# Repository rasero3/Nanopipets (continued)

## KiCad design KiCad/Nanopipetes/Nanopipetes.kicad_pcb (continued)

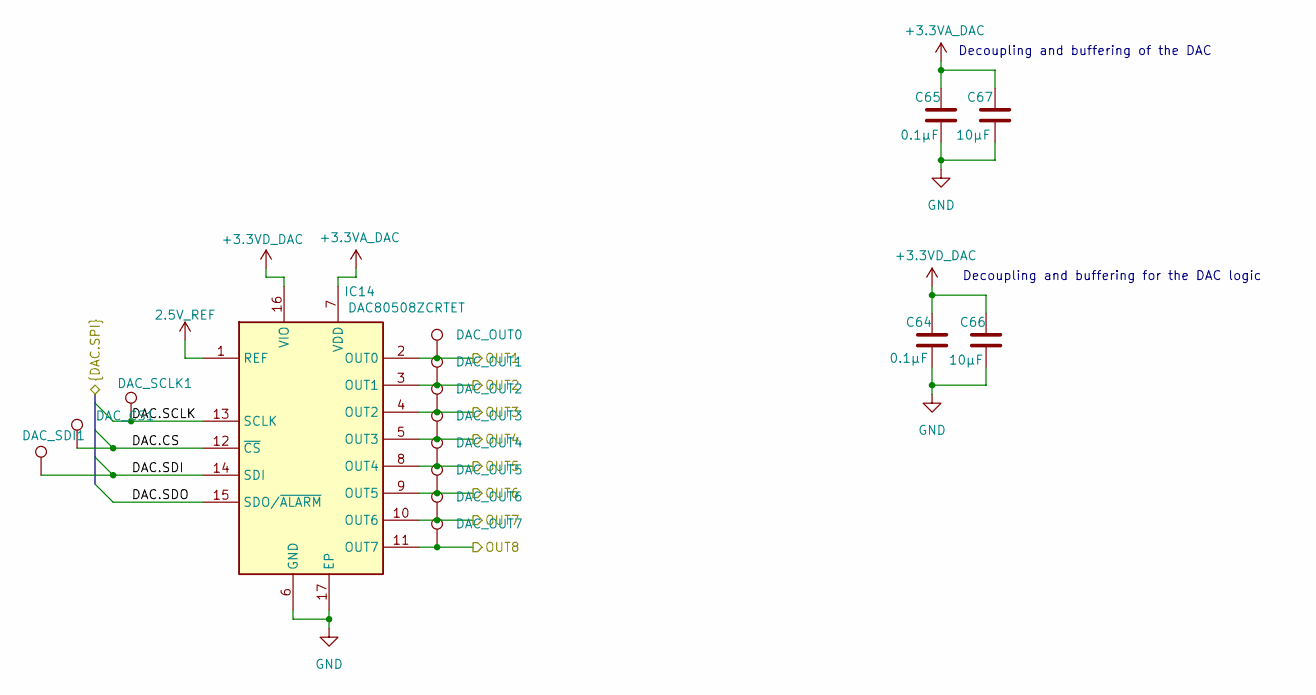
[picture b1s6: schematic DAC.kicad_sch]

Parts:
C64, C65: 0.1µF; C_0402_1005Metric; Mouser Part Number 581-0402YC104JAT4A
C66, C67: 10µF; C_0603_1608Metric; Mouser Part Number 80-C0603C106J3RACTU
DAC_CS1: TestPoint; TestPoint_Keystone_5000-5004_Miniature
DAC_OUT0, DAC_OUT1, DAC_OUT2, DAC_OUT3, DAC_OUT4, DAC_OUT5, DAC_OUT6, DAC_OUT7: TestPoint; TestPoint_Keystone_5000-5004_Miniature
DAC_SCLK1: TestPoint; TestPoint_Keystone_5000-5004_Miniature
DAC_SDI1: TestPoint; TestPoint_Keystone_5000-5004_Miniature
IC14: DAC80508ZCRTET; QFN50P300X300X80-17N; Manufacturer_Part_Number DAC80508ZCRTET; Mouser Part Number 595-DAC80508ZCRTET

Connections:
2.5V_REF: IC14.1 (REF); also elsewhere on the board
+3.3VA_ADC: C65.1, C67.1, IC14.7 (VDD); also elsewhere on the board
+3.3VD_ADC: C64.1, C66.1, IC14.16 (VIO); also elsewhere on the board
/DAC/DAC.CS: DAC_CS1.1, IC14.12 (~CS); also elsewhere on the board
/DAC/DAC.SCLK: DAC_SCLK1.1, IC14.13 (SCLK); also elsewhere on the board
/DAC/DAC.SDI: DAC_SDI1.1, IC14.14 (SDI); also elsewhere on the board
/DAC/DAC.SDO: IC14.15 (SDO/~ALARM); also elsewhere on the board
/DAC/OUT1: DAC_OUT0.1, IC14.2 (OUT0); also elsewhere on the board
/DAC/OUT2: DAC_OUT1.1, IC14.3 (OUT1); also elsewhere on the board
/DAC/OUT3: DAC_OUT2.1, IC14.4 (OUT2); also elsewhere on the board
/DAC/OUT4: DAC_OUT3.1, IC14.5 (OUT3); also elsewhere on the board
/DAC/OUT5: DAC_OUT4.1, IC14.8 (OUT4); also elsewhere on the board
/DAC/OUT6: DAC_OUT5.1, IC14.9 (OUT5); also elsewhere on the board
/DAC/OUT7: DAC_OUT6.1, IC14.10 (OUT6); also elsewhere on the board
/DAC/OUT8: DAC_OUT7.1, IC14.11 (OUT7); also elsewhere on the board
GND: C64.2, C65.2, C66.2, C67.2, IC14.6 (GND), IC14.17 (EP); also elsewhere on the board

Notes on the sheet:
Decoupling and buffering of the DAC
Decoupling and buffering for the DAC logic

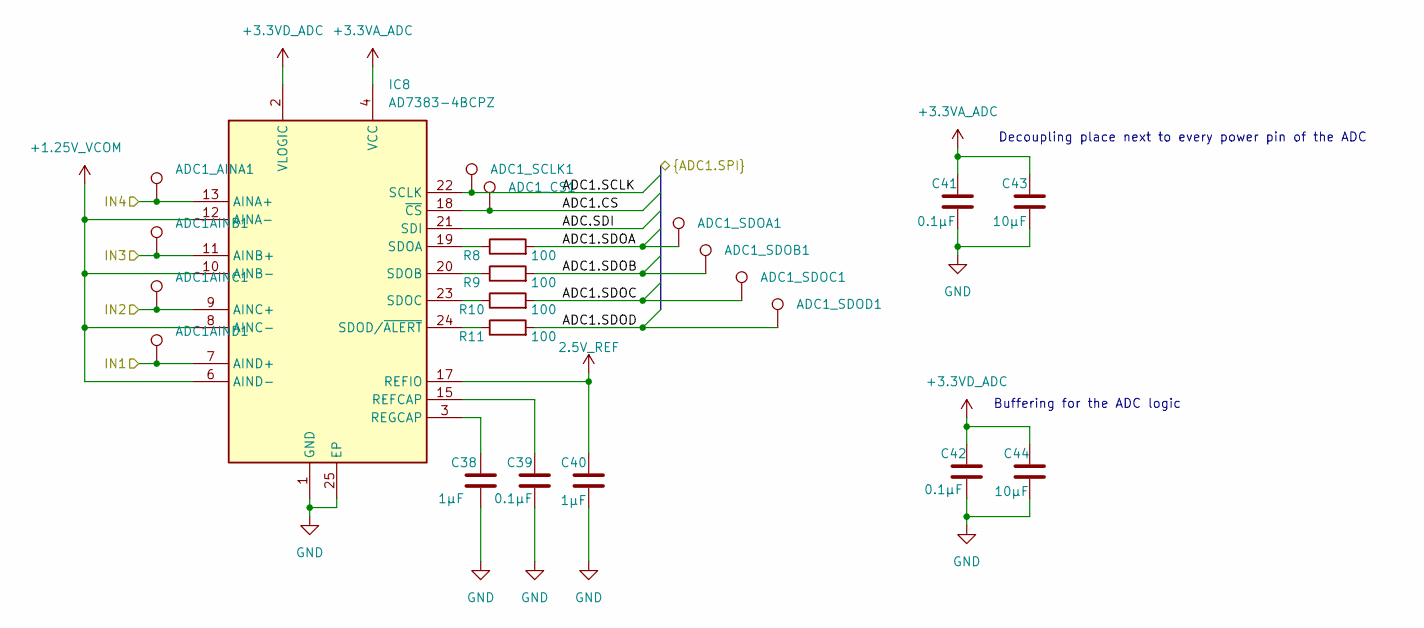
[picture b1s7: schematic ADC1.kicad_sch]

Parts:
ADC1AINB1, ADC1AINC1, ADC1AIND1, ADC1_AINA1, ADC1_CS1, ADC1_SCLK1, ADC1_SDOA1, ADC1_SDOB1, ADC1_SDOC1, ADC1_SDOD1: TestPoint; TestPoint_Keystone_5000-5004_Miniature
C38: 1µF; C_0402_1005Metric; Mouser Part Number 581-0402YC104JAT4A
C39, C41, C42: 0.1µF; C_0402_1005Metric; Mouser Part Number 581-0402YC104JAT4A
C40: 1µF; C_0603_1608Metric; Mouser Part Number 581-KGM15BR71A105JT
C43, C44: 10µF; C_0603_1608Metric; Mouser Part Number 80-C0603C106J3RACTU
IC8: AD7383-4BCPZ; QFN50P400X400X60-25N-D; Manufacturer_Part_Number AD7383-4BCPZ; Mouser Part Number 584-AD7383-4BCPZ
R8, R9, R10, R11: 100; R_0603_1608Metric; Mouser Part Number 71-RCG0603100RJNEA

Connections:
2.5V_REF: C40.1, IC8.17 (REFIO); also elsewhere on the board
+1.25V_VCOM: IC8.6 (AIND-), IC8.8 (AINC-), IC8.10 (AINB-), IC8.12 (AINA-); also elsewhere on the board
+3.3VA_ADC: C41.1, C43.1, IC8.4 (VCC); also elsewhere on the board
+3.3VD_ADC: C42.1, C44.1, IC8.2 (VLOGIC); also elsewhere on the board
/ADC1/ADC1.CS: ADC1_CS1.1, IC8.18 (~CS); also elsewhere on the board
/ADC1/ADC1.SCLK: ADC1_SCLK1.1, IC8.22 (SCLK); also elsewhere on the board
/ADC1/ADC1.SDOA: ADC1_SDOA1.1, R8.2; also elsewhere on the board
/ADC1/ADC1.SDOB: ADC1_SDOB1.1, R9.2; also elsewhere on the board
/ADC1/ADC1.SDOC: ADC1_SDOC1.1, R10.2; also elsewhere on the board
/ADC1/ADC1.SDOD: ADC1_SDOD1.1, R11.2; also elsewhere on the board
/ADC1/ADC.SDI: IC8.21 (SDI); also elsewhere on the board
/ADC1/IN1: ADC1AIND1.1, IC8.7 (AIND+); also elsewhere on the board
/ADC1/IN2: ADC1AINC1.1, IC8.9 (AINC+); also elsewhere on the board
/ADC1/IN3: ADC1AINB1.1, IC8.11 (AINB+); also elsewhere on the board
/ADC1/IN4: ADC1_AINA1.1, IC8.13 (AINA+); also elsewhere on the board
GND: C38.2, C39.2, C40.2, C41.2, C42.2, C43.2, C44.2, IC8.1 (GND), IC8.5 (GND_2), IC8.14 (GND_3), IC8.16 (GND_4), IC8.25 (EP); also elsewhere on the board
unnamed: C39.1, IC8.15 (REFCAP)
unnamed: C38.1, IC8.3 (REGCAP)
unnamed: IC8.19 (SDOA), R8.1
unnamed: IC8.20 (SDOB), R9.1
unnamed: IC8.23 (SDOC), R10.1
unnamed: IC8.24 (SDOD/~ALERT), R11.1

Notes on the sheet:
Buffering for the ADC logic
Decoupling place next to every power pin of the ADC

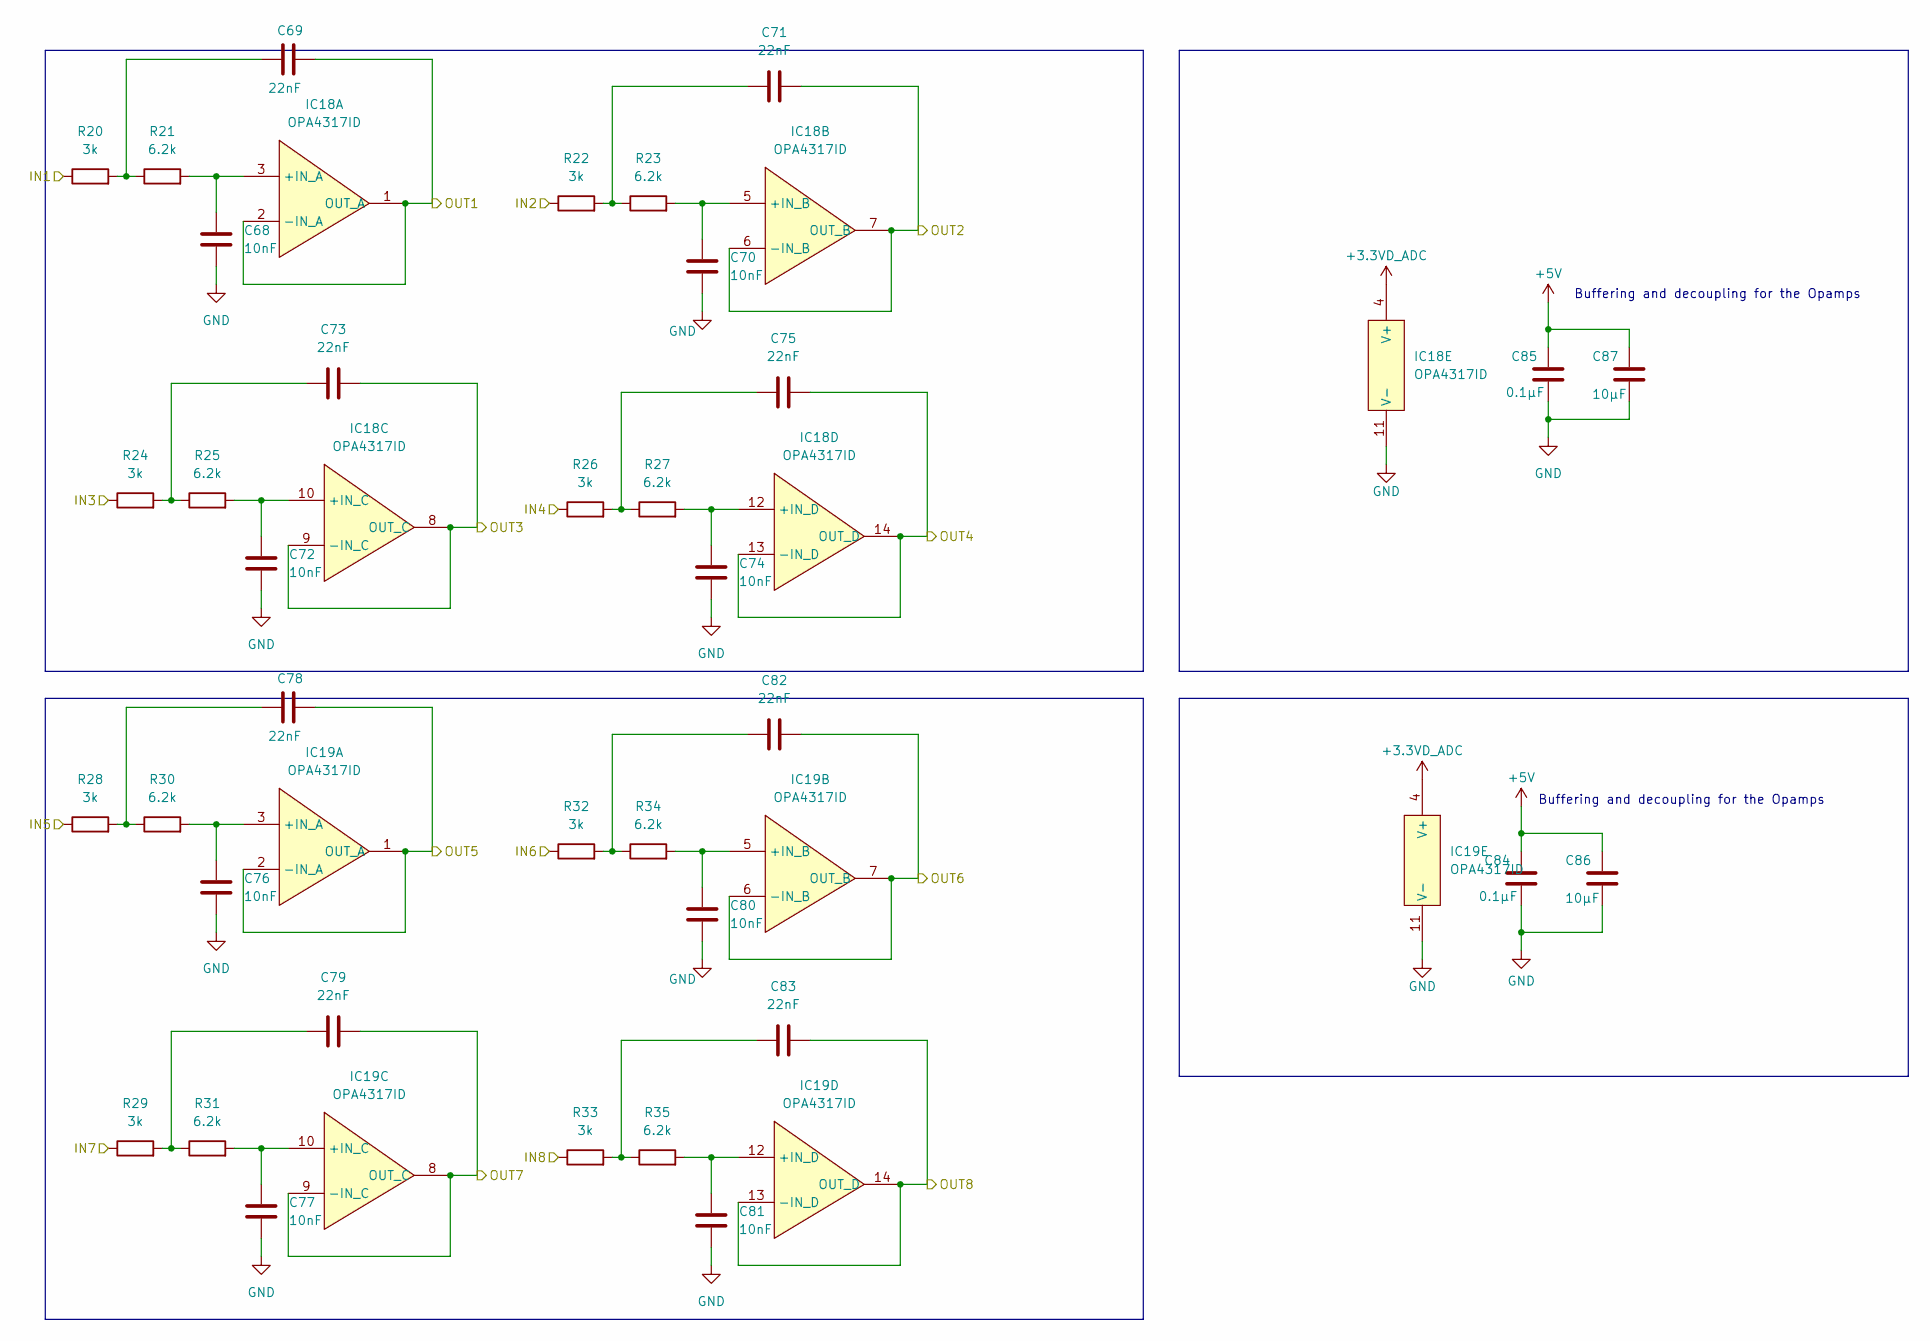
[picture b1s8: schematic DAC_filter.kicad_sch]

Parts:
C68, C70, C72, C74, C76, C77, C80, C81: 10nF; C_0402_1005Metric; Mouser Part Number 77-VJ0402Y103JXXAC
C69, C71, C73, C75, C78, C79, C82, C83: 22nF; C_0402_1005Metric; Mouser Part Number 581-04023C223JAT2A
C84, C85: 0.1µF; C_0402_1005Metric; Mouser Part Number 581-0402YC104JAT4A
C86, C87: 10µF; C_0603_1608Metric; Mouser Part Number 80-C0603C106J3RACTU
IC18, IC19: OPA4317ID; SOIC127P600X175-14N; Mouser Part Number 595-OPA4317ID
R20, R22, R24, R26, R28, R29, R32, R33: 3k; R_0603_1608Metric; Mouser Part Number 603-AR0603JR-073KL
R21, R23, R25, R27, R30, R31, R34, R35: 6.2k; R_0603_1608Metric; Mouser Part Number 603-AC0603JR-076K2L

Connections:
+3.3VD_ADC: IC18.4 (V+), IC19.4 (V+); also elsewhere on the board
+5V: C84.1, C85.1, C86.1, C87.1; also elsewhere on the board
/Connectors/OUT1: C69.2, IC18.1 (OUT_A), IC18.2 (-IN_A); also elsewhere on the board
/Connectors/OUT2: C71.2, IC18.6 (-IN_B), IC18.7 (OUT_B); also elsewhere on the board
/Connectors/OUT3: C73.2, IC18.8 (OUT_C), IC18.9 (-IN_C); also elsewhere on the board
/Connectors/OUT4: C75.2, IC18.13 (-IN_D), IC18.14 (OUT_D); also elsewhere on the board
/Connectors/OUT5: C78.2, IC19.1 (OUT_A), IC19.2 (-IN_A); also elsewhere on the board
/Connectors/OUT6: C82.2, IC19.6 (-IN_B), IC19.7 (OUT_B); also elsewhere on the board
/Connectors/OUT7: C79.2, IC19.8 (OUT_C), IC19.9 (-IN_C); also elsewhere on the board
/Connectors/OUT8: C83.2, IC19.13 (-IN_D), IC19.14 (OUT_D); also elsewhere on the board
/DAC/OUT1: R20.1; also elsewhere on the board
/DAC/OUT2: R22.1; also elsewhere on the board
/DAC/OUT3: R24.1; also elsewhere on the board
/DAC/OUT4: R26.1; also elsewhere on the board
/DAC/OUT5: R28.1; also elsewhere on the board
/DAC/OUT6: R32.1; also elsewhere on the board
/DAC/OUT7: R29.1; also elsewhere on the board
/DAC/OUT8: R33.1; also elsewhere on the board
GND: C68.2, C70.2, C72.2, C74.2, C76.2, C77.2, C80.2, C81.2, C84.2, C85.2, C86.2, C87.2, IC18.11 (V-), IC19.11 (V-); also elsewhere on the board
unnamed: C69.1, R20.2, R21.1
unnamed: C71.1, R22.2, R23.1
unnamed: C73.1, R24.2, R25.1
unnamed: C75.1, R26.2, R27.1
unnamed: C78.1, R28.2, R30.1
unnamed: C79.1, R29.2, R31.1
unnamed: C82.1, R32.2, R34.1
unnamed: C83.1, R33.2, R35.1
unnamed: C68.1, IC18.3 (+IN_A), R21.2
unnamed: C70.1, IC18.5 (+IN_B), R23.2
unnamed: C72.1, IC18.10 (+IN_C), R25.2
unnamed: C74.1, IC18.12 (+IN_D), R27.2
unnamed: C76.1, IC19.3 (+IN_A), R30.2
unnamed: C80.1, IC19.5 (+IN_B), R34.2
unnamed: C77.1, IC19.10 (+IN_C), R31.2
unnamed: C81.1, IC19.12 (+IN_D), R35.2

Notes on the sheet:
Buffering and decoupling for the Opamps

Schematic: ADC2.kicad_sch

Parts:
ADC2SDOD1, ADC2_AINA1, ADC2_AINB1, ADC2_AINC1, ADC2_AIND1, ADC2_CS1, ADC2_SCLK1, ADC2_SDOA1, ADC2_SDOB1, ADC2_SDOC1: TestPoint; TestPoint_Keystone_5000-5004_Miniature
C57: 1µF; C_0402_1005Metric; Mouser Part Number 581-0402YC104JAT4A
C58, C60, C61: 0.1µF; C_0402_1005Metric; Mouser Part Number 581-0402YC104JAT4A
C59: 1µF; C_0603_1608Metric; Mouser Part Number 581-KGM15BR71A105JT
C62, C63: 10µF; C_0603_1608Metric; Mouser Part Number 80-C0603C106J3RACTU
IC13: AD7383-4BCPZ; QFN50P400X400X60-25N-D; Manufacturer_Part_Number AD7383-4BCPZ; Mouser Part Number 584-AD7383-4BCPZ
R16, R17, R18, R19: 100; R_0603_1608Metric; Mouser Part Number 71-RCG0603100RJNEA

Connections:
2.5V_REF: C59.1, IC13.17 (REFIO); also elsewhere on the board
+1.25V_VCOM: IC13.6 (AIND-), IC13.8 (AINC-), IC13.10 (AINB-), IC13.12 (AINA-); also elsewhere on the board
+3.3VA_ADC: C60.1, C63.1, IC13.4 (VCC); also elsewhere on the board
+3.3VD_ADC: C61.1, C62.1, IC13.2 (VLOGIC); also elsewhere on the board
/ADC2/ADC2.CS: ADC2_CS1.1, IC13.18 (~CS); also elsewhere on the board
/ADC2/ADC2.SCLK: ADC2_SCLK1.1, IC13.22 (SCLK); also elsewhere on the board
/ADC2/ADC2.SDI: IC13.21 (SDI); also elsewhere on the board
/ADC2/ADC2.SDOA: ADC2_SDOA1.1, R16.2; also elsewhere on the board
/ADC2/ADC2.SDOB: ADC2_SDOB1.1, R17.2; also elsewhere on the board
/ADC2/ADC2.SDOC: ADC2_SDOC1.1, R18.2; also elsewhere on the board
/ADC2/ADC2.SDOD: ADC2SDOD1.1, R19.2; also elsewhere on the board
/ADC2/IN5: ADC2_AIND1.1, IC13.7 (AIND+); also elsewhere on the board
/ADC2/IN6: ADC2_AINC1.1, IC13.9 (AINC+); also elsewhere on the board
/ADC2/IN7: ADC2_AINB1.1, IC13.11 (AINB+); also elsewhere on the board
/ADC2/IN8: ADC2_AINA1.1, IC13.13 (AINA+); also elsewhere on the board
GND: C57.2, C58.2, C59.2, C60.2, C61.2, C62.2, C63.2, IC13.1 (GND), IC13.5 (GND_2), IC13.14 (GND_3), IC13.16 (GND_4), IC13.25 (EP); also elsewhere on the board
unnamed: C58.1, IC13.15 (REFCAP)
unnamed: C57.1, IC13.3 (REGCAP)
unnamed: IC13.19 (SDOA), R16.1
unnamed: IC13.20 (SDOB), R17.1
unnamed: IC13.23 (SDOC), R18.1
unnamed: IC13.24 (SDOD/~ALERT), R19.1

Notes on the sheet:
Buffering for the ADC logic
Decoupling place next to every power pin of the ADC

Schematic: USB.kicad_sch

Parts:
C134, C136: 27pF; C_0402_1005Metric; Mouser Part Number 80-C0402T270J3GACTU
C135: 10nF; C_0402_1005Metric; Mouser Part Number 77-VJ0402Y103JXXAC
C137, C139, C141, C142, C143, C144, C145, C146, C147, C148: 0.1µF; C_0402_1005Metric; Mouser Part Number 581-0402YC104JAT4A
C138, C140: 4.7µF; CP_EIA-3216-12_Kemet-S; Mouser Part Number 71-293D475X5010A2TE3
IC17: M93C46-WMN6TP; SOIC127P600X175-8N; Manufacturer_Part_Number M93C46-WMN6TP; Mouser Part Number 511-M93C46-WMN6TP
J2: USB_A; TECONN-4POS-USB; Mouser Part Number 640-USB1015-GF-L-A
R36: 0; R_0603_1608Metric
R55, R56, R58, R60: 10K; R_0603_1608Metric; Mouser Part Number 71-RCA060310K0JNEA
R57: 0; R_0603_1608Metric; Mouser Part Number 791-WR06X000PTR; not fitted
R59: 2.2K; R_0603_1608Metric; Mouser Part Number 71-CRCW06032K20JNEBC
R61: 12K; R_0603_1608Metric; Mouser Part Number 71-CRCW0603J-12K
U9: FT2232HQ; QFN-64-1EP_9x9mm_P0.5mm_EP4.35x4.35mm
Y2: 12MHz; ABM3; Mouser Part Number 815-ABM3-12-D2Y-T

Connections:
+1.8VD: C146.2, C147.2, C148.2, U9.12 (VCORE), U9.37 (VCORE), U9.64 (VCORE); also elsewhere on the board
+3.3V_USB: C137.2, C138.1, C139.2, C140.1, C141.2, C142.2, C143.2, C144.2, C145.2, IC17.8 (VCC), R55.1, R56.1, R58.1, R60.1, U9.4 (VPHY), U9.9 (VPLL), U9.20 (VCCIO), U9.31 (VCCIO), U9.42 (VCCIO), U9.56 (VCCIO); also elsewhere on the board
+5V: R57.2; also elsewhere on the board
/FPGA/USB.CLKOUT: U9.32 (ACBUS5); also elsewhere on the board
/FPGA/USB.D0: U9.16 (ADBUS0); also elsewhere on the board
/FPGA/USB.D1: U9.17 (ADBUS1); also elsewhere on the board
/FPGA/USB.D2: U9.18 (ADBUS2); also elsewhere on the board
/FPGA/USB.D3: U9.19 (ADBUS3); also elsewhere on the board
/FPGA/USB.D4: U9.21 (ADBUS4); also elsewhere on the board
/FPGA/USB.D5: U9.22 (ADBUS5); also elsewhere on the board
/FPGA/USB.D6: U9.23 (ADBUS6); also elsewhere on the board
/FPGA/USB.D7: U9.24 (ADBUS7); also elsewhere on the board
/FPGA/USB.OE#: U9.33 (ACBUS6); also elsewhere on the board
/FPGA/USB.RD#: U9.28 (ACBUS2); also elsewhere on the board
/FPGA/USB.RXD: U9.39 (BDBUS1); also elsewhere on the board
/FPGA/USB.RXF#: U9.26 (ACBUS0); also elsewhere on the board
/FPGA/USB.SWIUA: U9.30 (ACBUS4); also elsewhere on the board
/FPGA/USB.TXD: U9.38 (BDBUS0); also elsewhere on the board
/FPGA/USB.TXE#: U9.27 (ACBUS1); also elsewhere on the board
/FPGA/USB.WR#: U9.29 (ACBUS3); also elsewhere on the board
/USB/D+: J2.3 (D+), U9.8 (DP)
/USB/D-: J2.2 (D-), U9.7 (DM)
/USB/OSCN: C136.1, U9.3 (OSCO), Y2.2
/USB/OSCP: C134.1, U9.2 (OSCI), Y2.1
GND: C134.2, C135.2, C136.2, C137.1, C138.2, C139.1, C140.2, C141.1, C142.1, C143.1, C144.1, C145.1, C146.1, C147.1, C148.1, IC17.5 (VSS), IC17.6 (ORG), IC17.7 (DU), R36.2, R61.2, U9.1 (GND), U9.5 (GND), U9.10 (AGND), U9.11 (GND), U9.13 (TEST), U9.15 (GND), U9.25 (GND), U9.35 (GND), U9.47 (GND), U9.51 (GND), U9.65 (GND); also elsewhere on the board
unnamed: IC17.2 (C), U9.62 (EECLK)
unnamed: IC17.3 (D), R56.2, R59.2, U9.61 (EEDATA)
unnamed: IC17.4 (Q), R55.2, R59.1
unnamed: IC17.1 (S), R58.2, U9.63 (EECS)
unnamed: J2.4 (GND), J2.5 (Shield), R36.1
unnamed: J2.1 (VBUS), R57.1
unnamed: R61.1, U9.6 (REF)
unnamed: C135.1, R60.2, U9.14 (~RESET)

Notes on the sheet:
Decoupling place next to every power pin
Buffering for the USB driver

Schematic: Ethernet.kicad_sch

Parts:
C121, C122: 33pF; C_0402_1005Metric; Mouser Part Number 581-0402NPO330JT2AT
C123, C124, C125, C126, C127, C128, C129, C130, C131, C132, C133: 0.1µF; C_0402_1005Metric; Mouser Part Number 581-0402YC104JAT4A
IC16: DEL-DP83867IRPAPT; QFP50P1200X1200X120-65N; Manufacturer_Part_Number DEL-DP83867IRPAPT
J1: Conn_01x05_Pin; PinHeader_1x05_P2.54mm_Vertical
R52: 1.5k; R_0402_1005Metric; Mouser Part Number 652-CR0603-JW-152ELF
R53: 11K; R_0603_1608Metric; Mouser Part Number 660-HV73V1JTTD113J
R54: 1M; R_0603_1608Metric; Mouser Part Number 755-SFR03EZPJ105
Y1: 25MHz; XTAL1140X470X330D1270L391X60N; Mouser Part Number 815-ABM325000B4YT

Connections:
+1.1V_ETH: C125.2, C128.2, C130.2, C132.2, IC16.8 (VDD1P1_1), IC16.29 (VDD1P1_2), IC16.42 (VDD1P1_3), IC16.58 (VDD1P1_4); also elsewhere on the board
+1.8VD: C124.2, C127.2, C129.2, C131.2, C133.2, IC16.17 (VDDA1P8_1), IC16.23 (VDDIO_1), IC16.41 (VDDIO_2), IC16.57 (VDDIO_3), IC16.59 (RESET_N), IC16.60 (INT/PWDN), IC16.64 (VDDA1P8_2), R52.1; also elsewhere on the board
+2.5V_ETH: C123.2, C126.2, IC16.4 (VDDA2P5_1), IC16.12 (VDDA2P5_2); also elsewhere on the board
/Connectors/LED0: IC16.63 (LED_0); also elsewhere on the board
/Connectors/LED1: IC16.62 (LED_1); also elsewhere on the board
/Connectors/LED2: IC16.61 (LED_2); also elsewhere on the board
/Connectors/TD_M_A: IC16.3 (TD_M_A); also elsewhere on the board
/Connectors/TD_M_B: IC16.6 (TD_M_B); also elsewhere on the board
/Connectors/TD_M_C: IC16.11 (TD_M_C); also elsewhere on the board
/Connectors/TD_M_D: IC16.14 (TD_M_D); also elsewhere on the board
/Connectors/TD_P_A: IC16.2 (TD_P_A); also elsewhere on the board
/Connectors/TD_P_B: IC16.5 (TD_P_B); also elsewhere on the board
/Connectors/TD_P_C: IC16.10 (TD_P_C); also elsewhere on the board
/Connectors/TD_P_D: IC16.13 (TD_P_D); also elsewhere on the board
/Ethernet/Ethernet.GTX_CLK: IC16.40 (GTX_CLK); also elsewhere on the board
/Ethernet/Ethernet.MDC: IC16.20 (MDC); also elsewhere on the board
/Ethernet/Ethernet.MDIO: IC16.21 (MDIO), R52.2; also elsewhere on the board
/Ethernet/Ethernet.RX0: IC16.44 (RX_D0); also elsewhere on the board
/Ethernet/Ethernet.RX1: IC16.45 (RX_D1); also elsewhere on the board
/Ethernet/Ethernet.RX2: IC16.46 (RX_D2); also elsewhere on the board
/Ethernet/Ethernet.RX3: IC16.47 (RX_D3); also elsewhere on the board
/Ethernet/Ethernet.RX_CLK: IC16.43 (RX_CLK); also elsewhere on the board
/Ethernet/Ethernet.RX_CTRL: IC16.53 (RX_DV/RX_CTRL); also elsewhere on the board
/Ethernet/Ethernet.TX0: IC16.38 (TX_D0); also elsewhere on the board
/Ethernet/Ethernet.TX1: IC16.37 (TX_D1); also elsewhere on the board
/Ethernet/Ethernet.TX2: IC16.36 (TX_D2); also elsewhere on the board
/Ethernet/Ethernet.TX3: IC16.35 (TX_D3); also elsewhere on the board
/Ethernet/Ethernet.TX_CTRL: IC16.52 (TX_EN/TX_CTRL); also elsewhere on the board
GND: C121.2, C122.2, C123.1, C124.1, C125.1, C126.1, C127.1, C128.1, C129.1, C130.1, C131.1, C132.1, C133.1, IC16.31 (TX_D7), IC16.32 (TX_D6), IC16.33 (TX_D5), IC16.34 (TX_D4), IC16.39 (TX_ER), IC16.48 (RX_D4/GPIO), IC16.49 (RX_D5/GPIO), IC16.50 (RX_D6/GPIO), IC16.51 (RXD_7/GPIO), IC16.54 (RX_ER/GPIO), IC16.55 (COL/GPIO), IC16.56 (CS/GPIO), IC16.65 (EP), R53.2; also elsewhere on the board
unnamed: IC16.25 (JTAG_CLK), J1.2
unnamed: IC16.28 (JTAG_TDI), J1.5
unnamed: IC16.26 (JTAG_TDO), J1.3
unnamed: IC16.27 (JTAG_TMS), J1.4
unnamed: IC16.24 (JTAG_TRSTN), J1.1
unnamed: IC16.15 (RBIAS), R53.1
unnamed: C121.1, IC16.19 (X_I), R54.1, Y1.2
unnamed: C122.1, IC16.18 (X_O), R54.2, Y1.1

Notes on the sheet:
1.8V PINS, place CAP near every pin
1.1V PINS, place CAP near every pin
2.5V PINS, place CAP near every pin

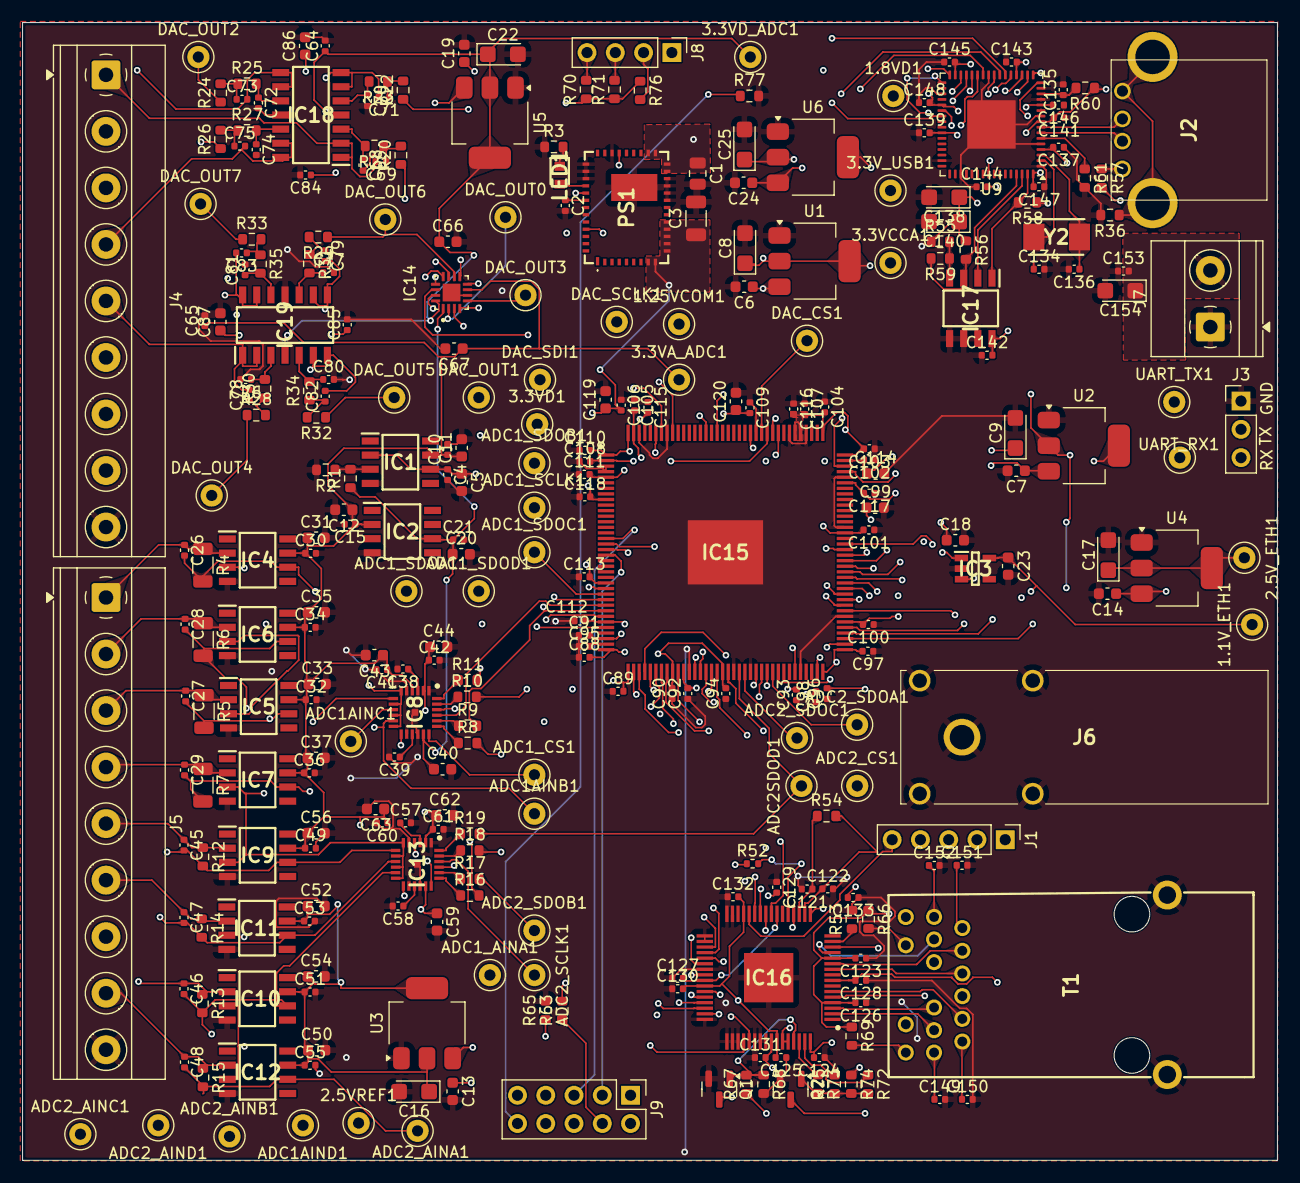
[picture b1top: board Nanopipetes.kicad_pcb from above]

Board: 4 copper layers, 112.8 x 102.2 mm, 298 parts (0 on the bottom side), 178 nets.

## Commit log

2025-09-30 Agregar nuevos contenidos de la carpeta
2025-11-24 Versión pre 24/11/2025
    Generación y leido de un voltaje estable por 8 canales
2025-11-24 Ramp v0.01
    Updating que output adding +1 integer every cycle
    Test Bench of a single channel
2025-11-26 Ramp V0.02
    Implemented 8 channel paralel output + ramp negative slope
    Old testbench reused
    Needs to fix:
    -Index reapeats the first number twice
2025-11-27 ramp v1.00
    Now the uart_flag activates the uart_state 3 when finished so it could start saving the info, when the matrix is full it will start generating the ramp (ramp generation still in developement)
    Also the uart might start sending the info by LSB first so the to_int conversion is easy-er
2025-11-27 ramp v1.01
    finished the block (receive uart inverted)
2025-11-28 Ramp v1.02
2025-12-01 MatLab
    The Matlab File was missing
    Pending:
    -not inverting the output
    -sending uart even when the voltaje is 0
2025-12-01 Expand project description in README
    Added details about the data flow and DAC functionality.
2025-12-01 ramp v1.03
    Finished receive file
    Experimental testing pending
2025-12-02 Cambios en KiCad
2025-12-02 kicad v 1.03
